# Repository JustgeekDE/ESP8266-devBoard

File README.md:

# ESP 8266 Dev board
A couple of different layouts for development boards for the ESP 8266 WiFi module.

## ESP8266-dev
This board is intended as a low cost, easy to build and source entry point to ESP 8266 development. After removing (or de-populating) the ESP part of the dev board, it can also be used with a different firmware as an AVR ISP programmer, SPI interface or for a variety of other uses.

However the AVR-CDC firmware is only reliable up to 4800 baud and can't reliably negotiate the 500 mA needed for the reliable operation.

## ESP8266-dev-ftdi
This is a small badge-like breakout board with onboard RGB LEDs. The aim of this board is to provide an easy to use playground for the V-01 version of the ESP 8266 module, while still being able to be used as a general interface board.

The chip reset of the ESP8266 is only released after the 500mA has been successfully negotiated.

Since a FT230X is used, the UART interface is lacking the DTR signal.

## Errata
- The USB socket on v0.1 of the FTDI board is a bit to far away from the board edge
- The RX and TX Leds on v0.1 of the FTDI board should be tied to VCC instead of GND

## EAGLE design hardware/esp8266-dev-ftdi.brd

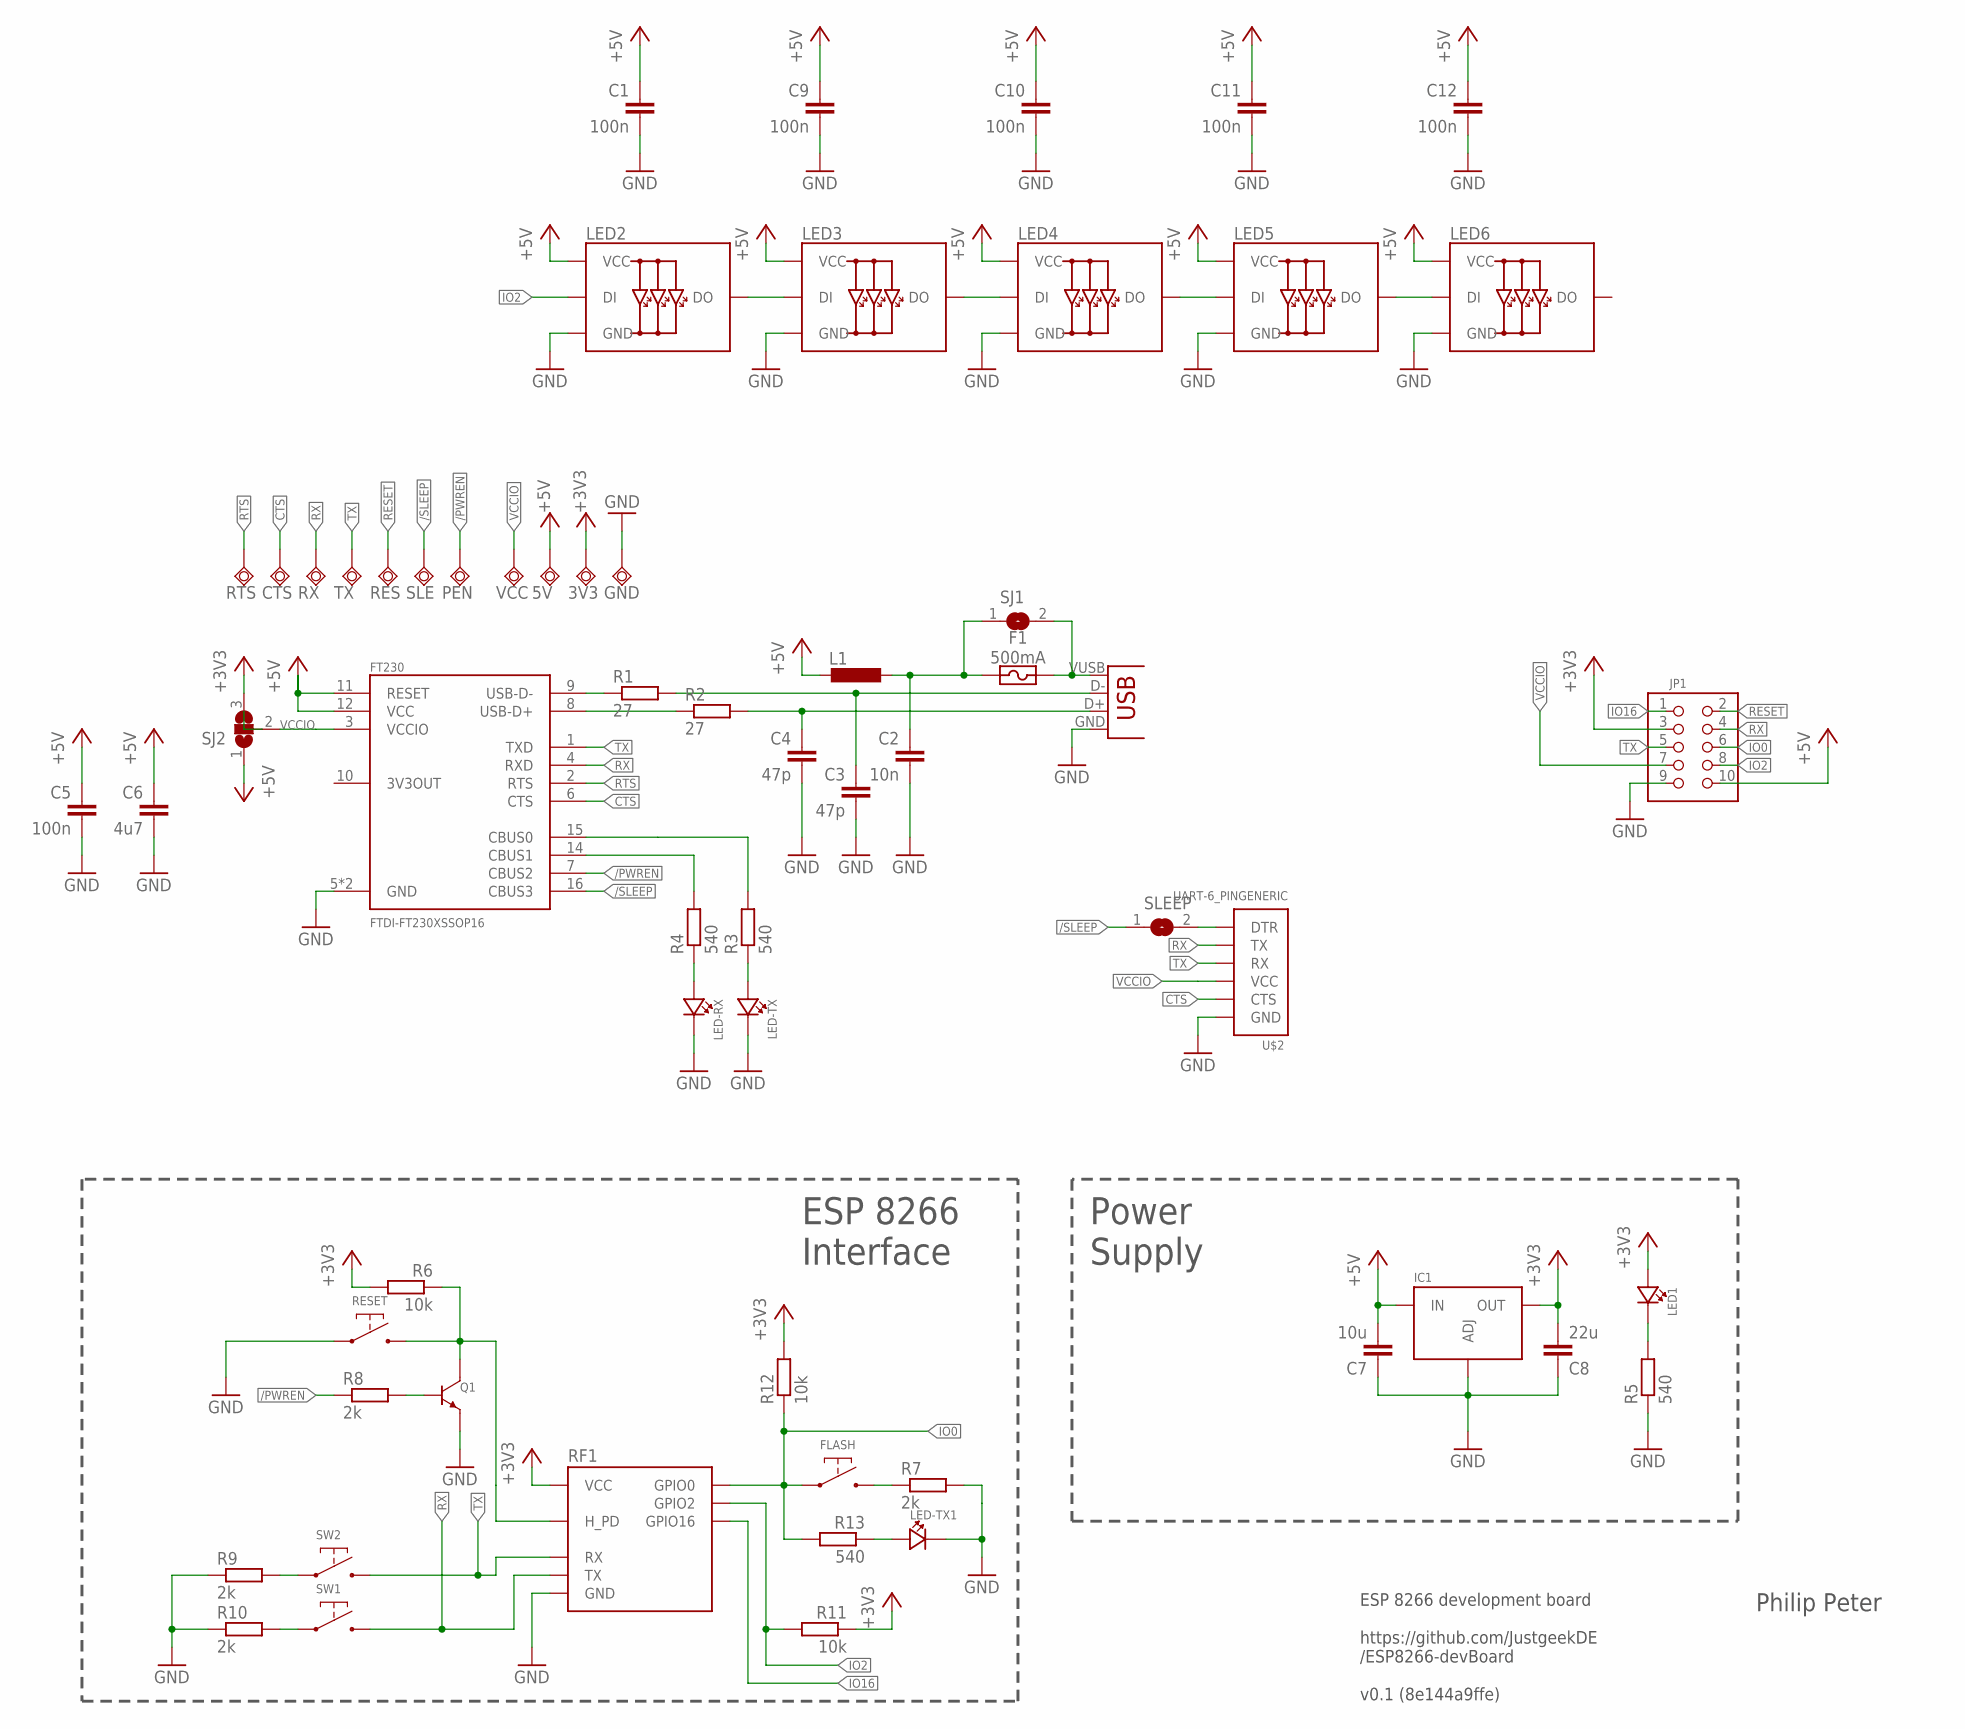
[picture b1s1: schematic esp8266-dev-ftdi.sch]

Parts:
3V3, 5V: TPSQTP15R; TP15R
C1, C5, C9, C10, C11, C12: 100n; C0805
C2: 10n; C0805
C3, C4: 47p; C0805
C6: 4u7; C0805
C7: 10u; C0805
C8: 22u; C0805
CON1: USBMICRO-NO_CENTER-LONG_PADS; USB-MICRO-SMD-NO_CENTER-LONG_PADS
CTS: TPSQTP15R; TP15R
F1: 500mA; SMD-FUSE-0805
FLASH: SWITCH-DEFAULT_OFF-DEFAULT; SWITCH-GENERIC-4_PIN
FT230: FTDI-FT230XSSOP16; SSOP-16-FTDI
GND: TPSQTP15R; TP15R
IC1: REGULATOR-LM317-SOT223; SOT223
JP1: GENERIC-2X5; PINHEADER-100MIL-2X5-NOSILK
L1: 875-MI0805K601R-10; R0805
LED1: LED0805; CHIPLED_0805
LED2, LED3, LED4, LED5, LED6: WS2812B; CHIP-5050-4_PIN
LED-RX: LED0805; CHIPLED_0805
LED-TX, LED-TX1: LED0805; CHIPLED_0805
PEN: TPSQTP15R; TP15R
Q1: TRANSISTOR-NPN-GENERIC-SOT23-BEC; SOT23
R1, R2: 27; R0805
R3, R4, R5, R13: 540; R0805
R6, R11, R12: 10k; R0805
R7, R8, R9, R10: 2k; R0805
RES: TPSQTP15R; TP15R
RESET: SWITCH-DEFAULT_OFF-2PIN; SWITCH-GENERIC-2_PIN
RF1: ESP2866-ESP-01THT; ESP8266-ESP-01
RTS: TPSQTP15R; TP15R
RX: TPSQTP15R; TP15R
SJ1: SJ
SJ2: SJ2W; SJ_2
SLE: TPSQTP15R; TP15R
SLEEP: SJ
SW1, SW2: SWITCH-DEFAULT_OFF-2PIN; SWITCH-GENERIC-2_PIN
TX: TPSQTP15R; TP15R
U$2: UART-6_PINGENERIC; PINHEADER-100MIL-1X6
VCC: TPSQTP15R; TP15R

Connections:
+3V3: 3V3.TP, C8.2, IC1.2 (OUT), IC1.4 (OUT), JP1.3, LED1.A, R6.2, R11.1, R12.2, RF1.VCC, SJ2.3
+5V: 5V.TP, C1.1, C5.1, C6.1, C7.2, C9.1, C10.1, C11.1, C12.1, FT230.11 (RESET), FT230.12 (VCC), IC1.3 (IN), JP1.10, L1.2, LED2.P$1 (VCC), LED3.P$1 (VCC), LED4.P$1 (VCC), LED5.P$1 (VCC), LED6.P$1 (VCC), SJ2.1
/PWREN: FT230.7 (CBUS2), PEN.TP, R8.1
/SLEEP: FT230.16 (CBUS3), SLE.TP, SLEEP.1
CTS: CTS.TP, FT230.6 (CTS), U$2.2 (CTS)
GND: C1.2, C2.2, C3.2, C4.2, C5.2, C6.2, C7.1, C8.1, C9.2, C10.2, C11.2, C12.2, CON1.GND, FT230.5 (GND), FT230.13 (GND), GND.TP, IC1.1 (ADJ), JP1.9, LED2.P$3 (GND), LED3.P$3 (GND), LED4.P$3 (GND), LED5.P$3 (GND), LED6.P$3 (GND), LED-RX.C, LED-TX.C, LED-TX1.C, Q1.P$2 (EMITTER), R5.1, R7.2, R9.1, R10.1, RESET.P$1, RF1.GND, U$2.1 (GND)
IO0: FLASH.P$1, FLASH.P$2, JP1.6, R12.1, R13.2, RF1.GPIO0
IO2: JP1.8, LED2.P$4 (DI), R11.2, RF1.GPIO2
IO16: JP1.1, RF1.GPIO16
unnamed: Q1.P$1 (BASE), R8.2
unnamed: C2.1, F1.1, L1.1, SJ1.1
unnamed: LED-TX.A, R3.1
unnamed: C3.1, CON1.D-, R1.2
unnamed: FT230.9 (USB-D-), R1.1
unnamed: FT230.8 (USB-D+), R2.1
unnamed: C4.1, CON1.D+, R2.2
unnamed: LED-RX.A, R4.1
unnamed: LED1.C, R5.2
unnamed: SLEEP.2, U$2.6 (DTR)
unnamed: FLASH.P$3, FLASH.P$4, R7.1
unnamed: LED2.P$2 (DO), LED3.P$4 (DI)
unnamed: FT230.15 (CBUS0), R3.2
unnamed: FT230.14 (CBUS1), R4.2
unnamed: LED3.P$2 (DO), LED4.P$4 (DI)
unnamed: LED4.P$2 (DO), LED5.P$4 (DI)
unnamed: LED5.P$2 (DO), LED6.P$4 (DI)
unnamed: CON1.VUSB (VBUS), F1.2, SJ1.2
unnamed: R9.2, SW2.P$1
unnamed: R10.2, SW1.P$1
unnamed: LED-TX1.A, R13.1
RESET: JP1.2, Q1.P$3 (COLLECTOR), R6.1, RES.TP, RESET.P$2, RF1.H_PD
RTS: FT230.2 (RTS), RTS.TP
RX: FT230.4 (RXD), JP1.4, RF1.TX, RX.TP, SW1.P$2, U$2.5 (TX)
TX: FT230.1 (TXD), JP1.5, RF1.RX, SW2.P$2, TX.TP, U$2.4 (RX)
VCCIO: FT230.3 (VCCIO), JP1.7, SJ2.2, U$2.3 (VCC), VCC.TP

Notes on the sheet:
ESP 8266 Interface
Power Supply
Philip Peter
ESP 8266 development board https://github.com/JustgeekDE /ESP8266-devBoard v0.1 (8e144a9ffe)

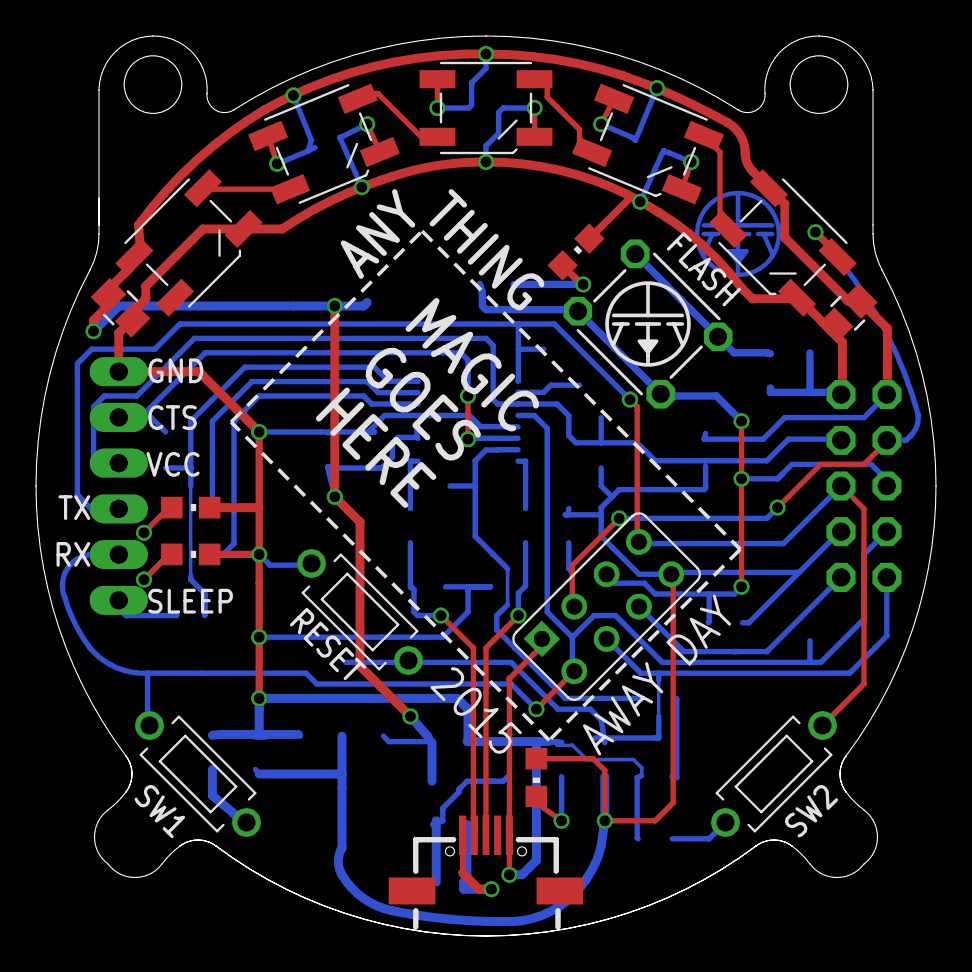
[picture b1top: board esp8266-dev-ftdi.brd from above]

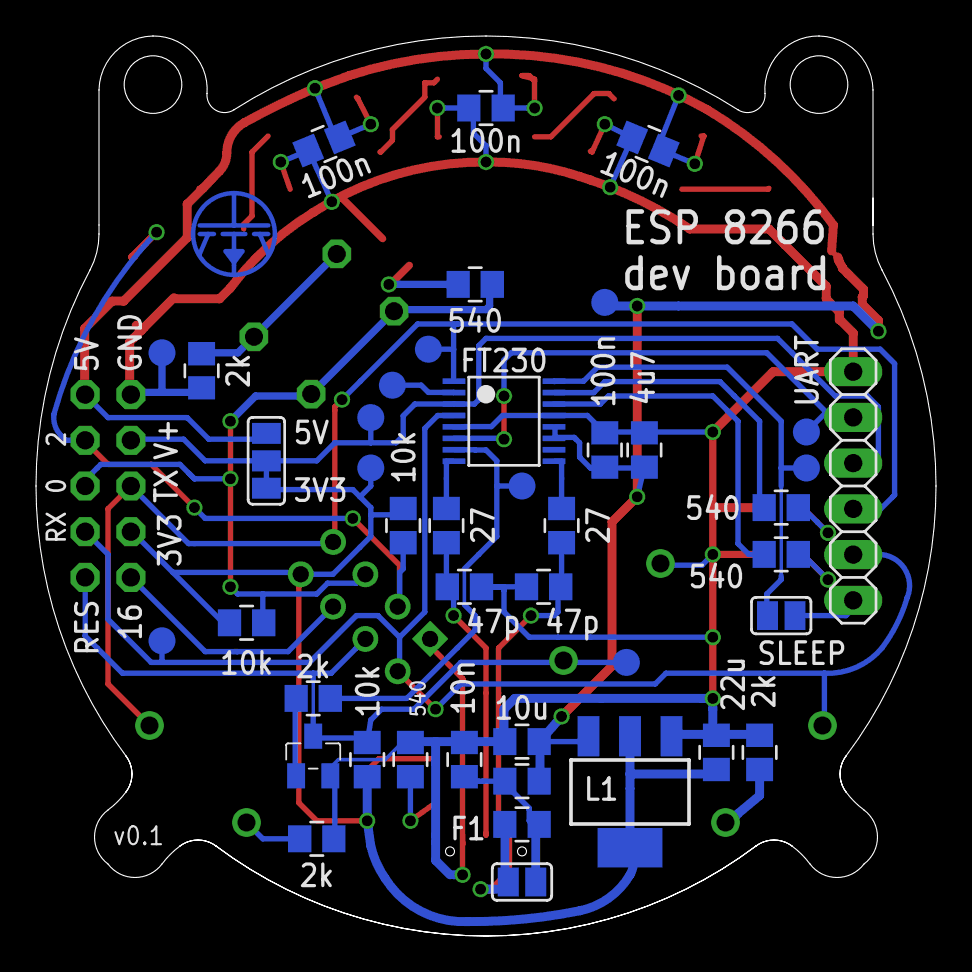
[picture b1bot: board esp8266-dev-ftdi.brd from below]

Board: 2 copper layers, 50.0 x 50.0 mm, 63 parts (45 on the bottom side), 35 nets.

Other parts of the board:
U$1: LOGO-JUSTGEEK-XS-PAD
U$3: LOGO-JUSTGEEK-XS

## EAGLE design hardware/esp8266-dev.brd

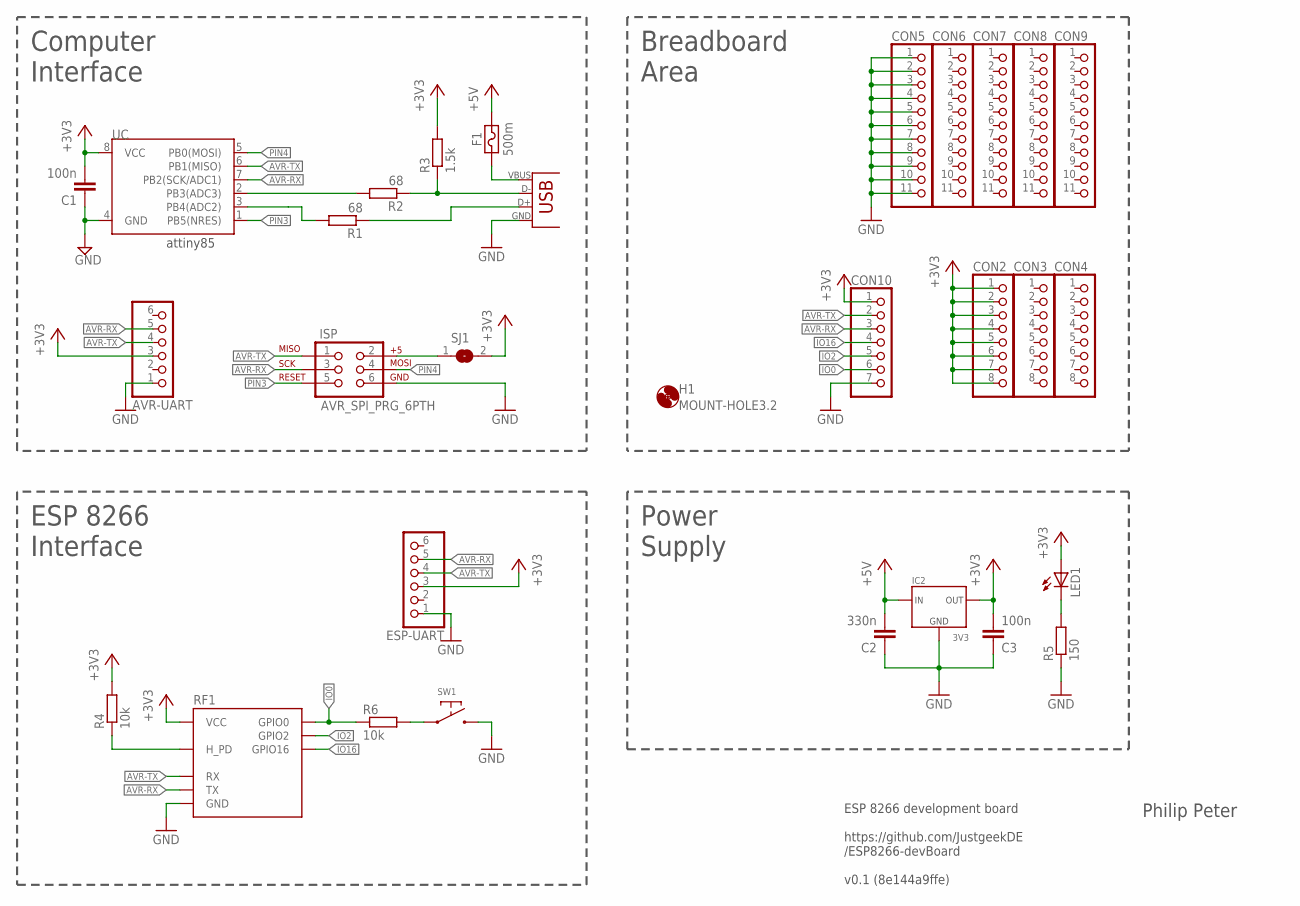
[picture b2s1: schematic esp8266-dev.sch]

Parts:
AVR-UART: GENERIC-1X6STANDARD; PINHEADER-100MIL-1X6
C1, C3: 100n; C025-025X050
C2: 330n; C025-025X050
CON1: USBB-SOCKET; PN61729-S
CON2, CON3, CON4: GENERIC-1X8NOSILK; PINHEADER-100MIL-1X8-NOSILK
CON5, CON6, CON7, CON8, CON9: GENERIC-1X11NOSILK; PINHEADER-100MIL-1X11-NOSILK
CON10: GENERIC-1X7NOSILK; PINHEADER-100MIL-1X7-NOSILK
ESP-UART: GENERIC-1X6STANDARD; PINHEADER-100MIL-1X6
F1: 500m; FUSE-THT-100-MIL
H1: MOUNT-HOLE3.2; 3,2
IC2: 3V3; TO220V
ISP: AVR_SPI_PRG_6PTH; 2X3
LED1: LED3MM
R1, R2: 68; 0204/7
R3: 1.5k; 0204/7
R4, R6: 10k; 0204/7
R5: 150; 0204/7
RF1: ESP2866-ESP-01THT-NOSILK; ESP8266-ESP-01-NOSILK
SJ1: SJ
SW1: SWITCH-DEFAULT_OFF-DEFAULT; SWITCH-GENERIC-4_PIN
UC: ATTINY85; DIP08

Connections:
+3V3: AVR-UART.3, C1.2, C3.2, CON2.1, CON2.2, CON2.3, CON2.4, CON2.5, CON2.6, CON2.7, CON2.8, CON10.1, ESP-UART.3, IC2.3 (OUT), LED1.A, R3.2, R4.2, RF1.VCC, SJ1.2, UC.8 (VCC)
+5V: C2.2, F1.P$2, IC2.1 (IN)
AVR-RX: AVR-UART.5, CON10.3, ESP-UART.5, ISP.3, RF1.TX, UC.7 (PB2(SCK/ADC1))
AVR-TX: AVR-UART.4, CON10.2, ESP-UART.4, ISP.1, RF1.RX, UC.6 (PB1(MISO))
D+: CON1.3 (D+), R1.1
D-: CON1.2 (D-), R2.1, R3.1
GND: AVR-UART.1, C1.1, C2.1, C3.1, CON1.4 (GND), CON5.1, CON5.2, CON5.3, CON5.4, CON5.5, CON5.6, CON5.7, CON5.8, CON5.9, CON5.10, CON5.11, CON10.7, ESP-UART.1, IC2.2 (GND), ISP.6, R5.1, RF1.GND, SW1.P$3, SW1.P$4, UC.4 (GND)
IO0: CON10.6, R6.1, RF1.GPIO0
IO2: CON10.5, RF1.GPIO2
IO16: CON10.4, RF1.GPIO16
unnamed: R2.2, UC.2 (PB3(ADC3))
unnamed: R1.2, UC.3 (PB4(ADC2))
unnamed: LED1.K (C), R5.2
unnamed: CON1.1 (VBUS), F1.P$1
unnamed: R4.1, RF1.H_PD
unnamed: R6.2, SW1.P$1, SW1.P$2
PIN3: ISP.5, UC.1 (PB5(NRES))
PIN4: ISP.4, UC.5 (PB0(MOSI))
VCC_HEADER: ISP.2, SJ1.1

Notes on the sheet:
attiny85
Computer Interface
ESP 8266 Interface
Breadboard Area
Power Supply
Philip Peter
ESP 8266 development board https://github.com/JustgeekDE /ESP8266-devBoard v0.1 (8e144a9ffe)

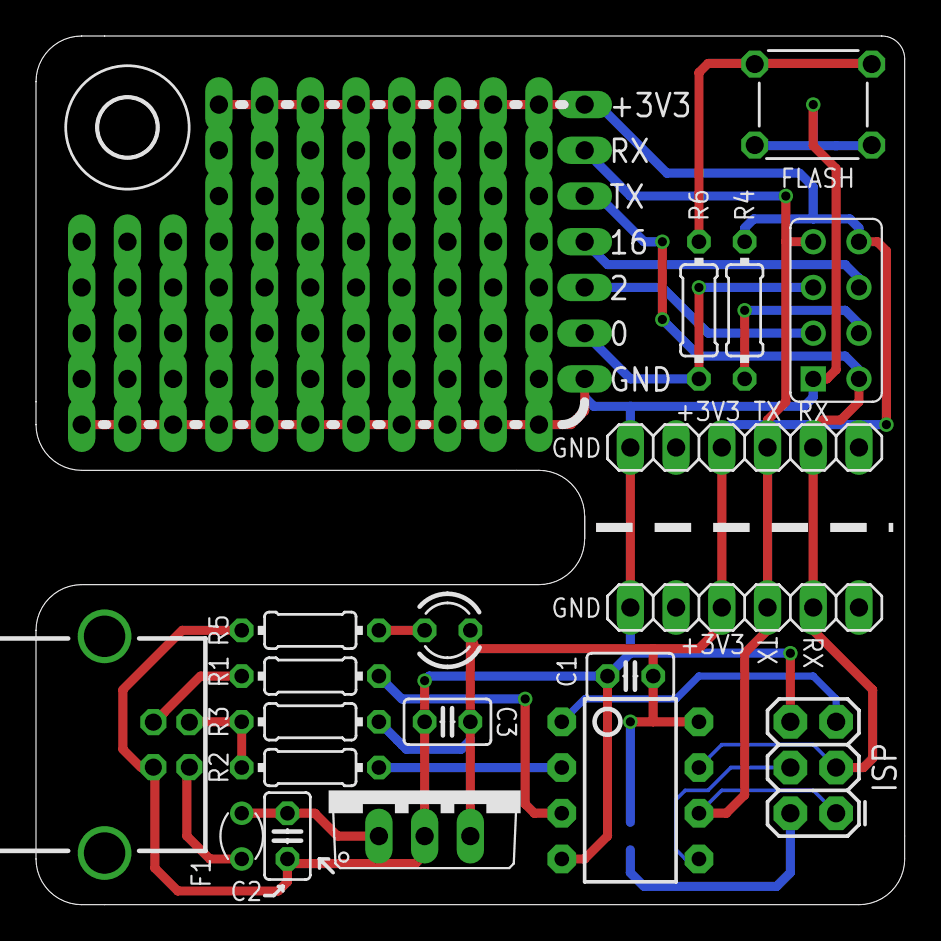
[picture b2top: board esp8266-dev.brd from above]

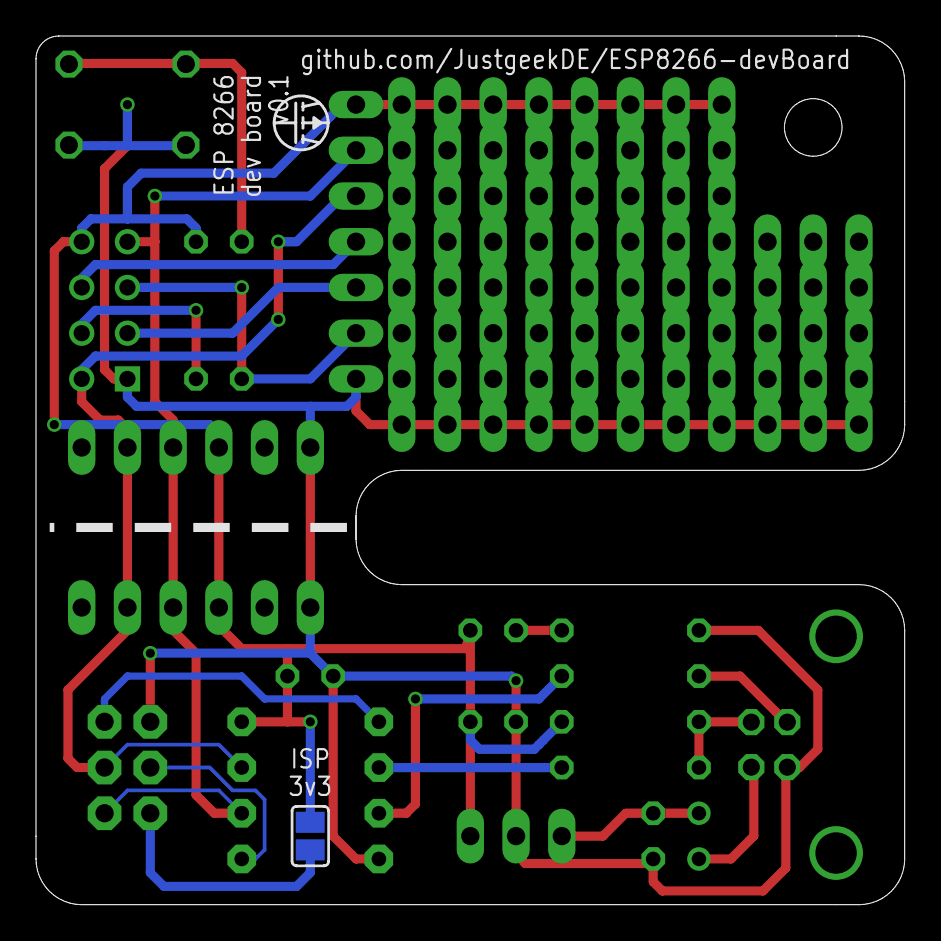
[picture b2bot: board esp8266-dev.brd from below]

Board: 2 copper layers, 48.3 x 48.3 mm, 31 parts (2 on the bottom side), 19 nets.

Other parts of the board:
U$3: LOGO-JUSTGEEK-XXXS

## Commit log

2015-04-01 Initial checkin
2015-04-03 Added eagle temp files to ignore
2015-04-03 Added notes, to keep track of todos
2015-04-03 generic little wire conversion complete
2015-04-04 Added ESP sub board with proto area
2015-04-04 Removed temp file from repo
2015-04-04 changed regulator to 500m suitable version and fuse to smaller footprint
2015-04-04 basic lazyout done, cleaning up silkscreen
2015-04-04 first acceptable layout, off to review
2015-04-05 Removed EAGLE project file from git
2015-04-05 Added more silkscreen
2015-04-05 git weirdness please ignore
2015-04-05 Further cleanup
2015-04-05 Also ignoring gerber files now
2015-04-05 Fixed silkscreen on board
2015-04-16 Cleaned up schematic
2015-04-16 Removed eagle project file from repo
2015-04-16 Added some documentation
2015-04-16 Started on description
2015-05-11 Working on FTDI based board
2015-05-19 Changed to FTDI module instead of discrete components
2015-05-19 Changed board dimensions
2015-05-20 Revert "Changed board dimensions"
    This reverts commit 250896ee29173e178886add8db11c26ec19ca707.
2015-05-20 Revert "Changed to FTDI module instead of discrete components"
    This reverts commit a00f7f1f84a57c5e7a19d78f77a78fc68ade4bc8.
2015-05-20 Added LEDs
2015-05-20 Updated todos
2015-05-21 added todo
2015-05-21 added result of snap to board to gitignore
2015-05-21 schematic mostly done
2015-05-21 new USB connector with longer pads
2015-05-21 starting layout
2015-05-21 board outline and orga
2015-05-21 LED power
2015-05-21 Everything routed
2015-05-22 Layout done
2015-05-22 added test pads
2015-05-22 minor cleanup
2015-05-22 adjusted dimensions to make mounting holes more robust
2015-05-22 silkscreen adjustments
2015-05-22 added led to gpio2
2015-05-22 basic layoutfor added components
2015-05-22 routed new components in layout
2015-05-22 fixed silkscreen for new components
2015-05-22 added notches for rubberbands to dimension
2015-05-22 cosmetics
2015-05-22 added decoupling caps for leds
2015-05-22 changed bottom values to place layer
2015-05-22 Increasing distance between pads and signals
2015-05-23 readme
2015-05-24 cleanup schematict
2015-05-24 cleanup documentation
2015-05-25 Initial checkin code base
2015-05-26 Basic blink examples
2015-05-27 Starting work on proxy to count hashtags
2015-05-27 Added node modules to gitignore
2015-05-27 debian compatible command
2015-05-27 playing around with twitter api
    adding debug logs to gitignore
2015-05-27 still trying to ignore things
2015-05-27 Started on hashtag count
2015-05-27 Basic interface done
2015-05-28 Basis for oauth
2015-05-28 Added test header for provisioning
2015-05-29 Added more Errata
2015-05-29 Basic color wheel as example for loops, conditions and WS2812b handling
2015-05-29 small hsv test script
2015-06-01 added simple init script
2015-06-06 changed test script to output mac
2015-06-06 example url query script
2015-06-06 moved node server to own repo
2015-06-06 Added example code snippets
